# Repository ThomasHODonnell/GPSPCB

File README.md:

# GPS PCB - designing a consumer electronic from start to finish

## *Concepts*
- My father run a bicycle shop. Some of his customers' bicycles have been stolen. He asked me if I could design a product to help combat this problem. This problem led me to a GPS based solution - to get things started. 
- The solution provided here is an embedded system that can transmit its location upon request utilizing a satallite HTTP request API.
- This product combats the problem by not only locating a stolen / lost bicycle, but my locating a potential thief. Therefore, this product can act as a form of location verification for law enforcement bodies in pursuit of any item this PCB is attached to. 

## *Logistics* 
- I have designed 3D printed CAD models to safely secure this system on a moving bicycle. This system comfortably holds the PCB, its components and a battery. 
- While I have not completed suffient testing to determine the battery life of this system, its power consumption is very low for a reasonably sized battery and its capacity. This combination should ensure that the device does not need to be recharged for a reasonable amount of time. 

## Technical Information
- This initial design is intended to be minimalistic. I have foregone a Microcontroller Unit in an effort to minimize power consumption, size, and cost. Alternativly, I have implemented a standalone Reciever / Transciever combination to complete the necessary funcitonality without any additional computing. 
- Of course, there are a number of other ICs to accompany these functional components, such as LDO Regulators, Operational Amplifiers, Logic Gates, Switches, Battery IC, Low Noise Amplifier, and Antennas.  
- While this Electronic Circuit requires significantly more testing, the technical aspectrs of this solution offer a helpful initial solution to a logicically challenging problem. 

## Disclaimer
- I am a third-year Computer Engineering Student. In no fashion am I qualified to develop professional grade products at this point in my career. 
- Therefore, I would not recommend using any of my design choices for other applications without inquiring a professional. 
- I will post other README files within other folders with other information, screenshots, and files.

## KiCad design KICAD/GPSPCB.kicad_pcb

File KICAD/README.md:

# Kicad Files

## *This folder contains files needed to open / edit this project in KICAD.* 

- I'll use these files to provide screenshots from the IMAGES folder for your entertainment!
- This file could also be considered as a BOM, but i'll leave out component prices as they fluctuate frequently. 
- The PCB should be finished with production within the next week or so (7/27/23), after which I will upload real images of the device.

### **Electrical Schematics** 

#### Complete Schematic

#### LDO and Battery IC
- LDO(1.8V): LT1963A - Linear Technology
-  Rechargable Battert IC: BQ24092 - T.I.

#### Reciever
- RF Reciever: STA8090FG - STM32MicroElectronics
- 

#### Transciever
- RF signal transciever: SX1268IMLTRT - Semtech Corp. 

#### Various Components
- Op-Amp: TL081HIDBVR - T.I.
- LNA: SKY65404-31 - Skyworks
- Input Antenna: 1575AT43A0040001E - Johanson
- SPDT RF Switch: PE4259 - Pasternack
- Output Antenna: A10340 - Antenova
- Dual NAND Gate: 74LVC2G00GT,115 - Nexperia
- Water Resistant USBC Port: DX07S016JA1R1500 - JAE Elec. 
- 32 MHZ Crystal: FC-12M 32.7680KD-A0 - EPSON

### **PCB Schematics**
- I will only show a screenshot of the Front Copper layer, as all of the components are located on this layer. 
- If interested, I welcome a detailed review of the PCB design through the direct file found in this folder. 
- DISCLAIMER: I AM NOT EMPLOYED BY PROTECTION AUTOMATED. I am interested in entrepreneurship in the future. 
If testing proves that a version of this product could become viable, I wanted to label the project as that businesses prototype. 

- A 3D view for a more clear image.

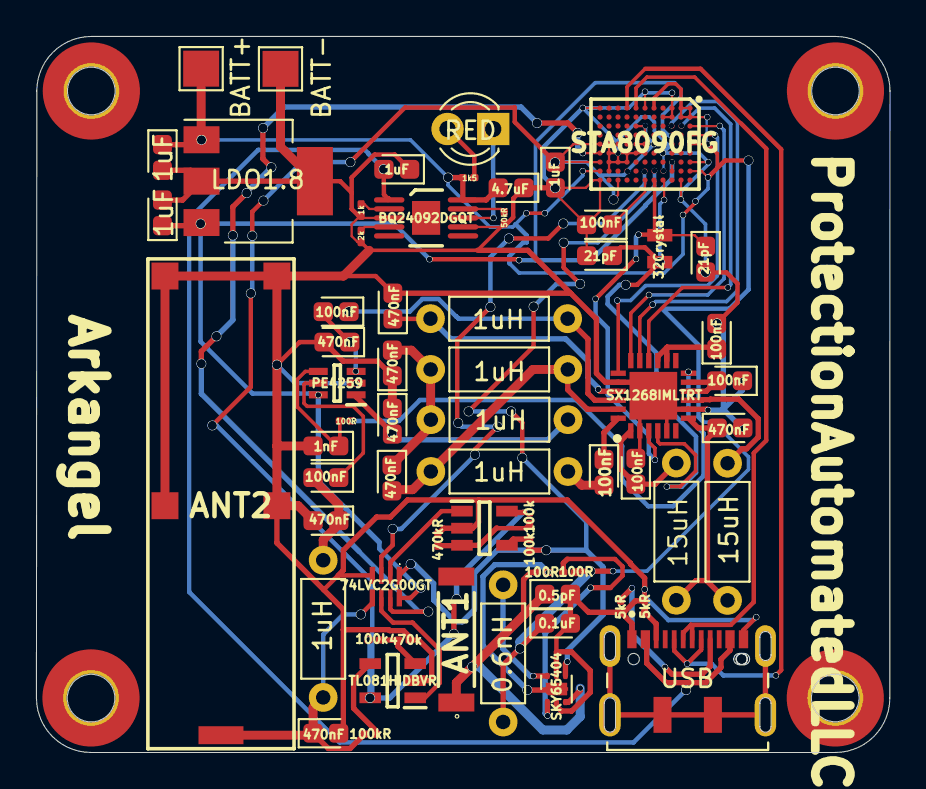
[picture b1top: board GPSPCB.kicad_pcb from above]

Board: 2 copper layers, 47.4 x 39.8 mm, 68 parts (0 on the bottom side), 52 nets.

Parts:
ANT1: 1575AT43A0040E
ANT2: A10340
C4, C5: 21pF; CP_EIA-1608-08_AVX-J
C6, C7, C11, C15: 1uF; CP_EIA-1608-08_AVX-J
C8: 0.1uF; CP_EIA-1608-08_AVX-J
C9: 0.5pF; CP_EIA-1608-08_AVX-J
C10: 4.7uF; CP_EIA-1608-08_AVX-J
C12, C16, C17, C18, C22, C24: 100nF; CP_EIA-1608-08_AVX-J
C13, C14, C19, C20, C21, C23, C25, C26: 470nF; CP_EIA-1608-08_AVX-J
C27: 1nF; CP_EIA-1608-08_AVX-J
Ce: 100nF; CP_EIA-1608-08_AVX-J
D2: RED; LED_D3.0mm
H1, H2, H3, H4: MountingHole; MountingHole_2.7mm_M2.5_Pad_TopOnly
IC1: STA8090FG; BGA99C50P9X11_500X600X120
IC2, IC5: TL081HIDBVR; SOT95P280X145-5N
IC3: SX1268IMLTRT; QFN50P400X400X100-25N-D
IC4: PE4259; SOT65P210X110-6N
IC6: 74LVC2G00GT; 74AVC9112GTX
J1: USB; JAE_DX07S016JA1R1500
L1: 0.6nH; L_Axial_L5.3mm_D2.2mm_P7.62mm_Horizontal_Vishay_IM-1
L2, L5, L7, L8: 1uH; L_Axial_L5.3mm_D2.2mm_P7.62mm_Horizontal_Vishay_IM-1
L3, L4: 15uH; L_Axial_L5.3mm_D2.2mm_P7.62mm_Horizontal_Vishay_IM-1
Le: 1uH; L_Axial_L5.3mm_D2.2mm_P7.62mm_Horizontal_Vishay_IM-1
R1, R3, R12: 100R; R_0201_0603Metric
R2, R8: 5kR; R_0201_0603Metric
R4: 1k; R_0201_0603Metric
R5: 2k; R_0201_0603Metric
R6: 50kR; R_0201_0603Metric
R7: 1k5; R_0201_0603Metric
R9, R11, R15: 100k; R_0201_0603Metric
R10: 470kR; R_0201_0603Metric
R14: 100kR; R_0201_0603Metric
R16: 470k; R_0201_0603Metric
TP1: BATT+; TestPoint_Pad_2.0x2.0mm
TP2: BATT-; TestPoint_Pad_2.0x2.0mm
U2: SKY65404; Skyworks_SKY65404-31
U3: LDO1.8; SOT-223-3_TabPin2
U4: BQ24092DGQT; DGQ0010D_NV_N
Y2: 32Crystal; FC12M327680KDA0

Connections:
+1V0: C6.1, C8.1, C10.2, IC1.A1 (VINM_1), IC1.A2 (VINM_2), IC1.A5 (VINL1), IC1.A8 (VINB), IC1.B1 (VLX_1), IC1.B2 (VLX_2), IC1.E1 (VDD_ANA), IC1.L8 (VINL2), L1.2, R3.2, R7.1, TP1.1, U3.1 (IN), U4.10 (OUT)
+1V1: C15.1, IC1.E5 (VDDD_1), IC1.F3 (VDDD_2), IC1.F4 (VDDD_3), IC1.G3 (VDDD_4), IC1.H8 (VCC_PLL), IC1.J9 (VCC_CHAIN), IC1.L5 (VCC_RF), IC1.L7 (VOL2), IC2.5 (V+), IC5.5 (V+), R9.1, R15.1
+1V5: C7.1, IC1.C4 (VDDIO__R1), IC1.C7 (VDD_SQI), IC1.C8 (VDD__ADC), IC4.6 (~CTRL_OR_VDD), IC6.8 (VCC), U3.3 (OUT)
-BATT: ANT2.1, ANT2.2, ANT2.3, ANT2.4, C4.2, C5.2, C6.2, C7.2, C8.2, C9.2, C10.1, C11.1, C12.2, C14.2, C15.2, C17.1, C18.2, C19.1, C20.1, C21.2, C23.2, C25.2, C26.2, C27.2, Ce.2, IC1.A7 (GND_1), IC1.B9 (GND_2), IC1.C1 (GND_3), IC1.C2 (GND_4), IC1.D2 (GND_5), IC1.D6 (GND_6), IC1.D8 (GND_7), IC1.F1 (GND_8), IC1.F5 (GND_9), IC1.F6 (GND_10), IC1.G4 (GND_11), IC1.G5 (GND_12), IC1.G6 (GND_13), IC1.H6 (GND_14), IC1.H7 (GND_15), IC1.J6 (GND_16), IC1.J7 (GND_17), IC1.K5 (GND_18), IC1.K6 (GND_19), IC1.K7 (GND_20), IC1.K8 (GND_LNA), IC1.L1 (GND_21), IC1.L9 (GND_22), IC2.2 (V-), IC3.2 (GND_1), IC3.5 (GND_2), IC3.8 (GND_3), IC3.20 (GND_4), IC3.25 (GND_5), IC4.2 (GND), IC5.2 (V-), IC6.4 (GND), J1.1 (GND), J1.12 (GND), R2.1, R4.2, R5.2, R6.2, R8.1, R10.2, R16.2, TP2.1, U2.2 (GND), U2.5 (GND), U3.2 (GND), U4.3 (VSS), U4.7 (ISET2)
ANTOUT: ANT2.5 (FEED), C26.1, IC6.5 (2A), L8.1, R14.1
BATTICIN: C11.2, J1.2 (VBUS), J1.11 (VBUS), U4.1 (IN)
CrystalA: C5.1, IC1.E9 (RTC_XTI), IC3.3 (XTA), Y2.1
CrystalB: C4.1, IC1.D9 (RTC_XTO), IC3.4 (XTB), Y2.2
D+: IC1.G1 (USB_DP), J1.6 (D+), J1.7 (D+)
D-: IC1.H1 (USB_DM), J1.5 (D-), J1.8 (D-)
DIO2: IC3.12 (DIO2), R12.2
LNA_IN: IC1.L6 (LNA_IN), IC6.7 (1Y)
LNA_OUT: IC1.E8 (WAKEUP0), IC6.1 (1A), R11.1, U2.4 (RFOUT)
MISO: IC1.B3 (SPI_DI), IC3.16 (MISO)
MOSI: IC1.C3 (SPI_DO), IC3.17 (MOSI)
NSS: IC1.A4 (SPI_CSN), IC3.19 (NSS)
unnamed: ANT1.1 (FEED), C9.1, R1.2, U2.3 (RFIN)
unnamed: C13.1, C19.2, L5.1, Le.2
unnamed: C16.2, L2.2
unnamed: C24.2, C25.1, L8.2
unnamed: D2.2 (A), R7.2
unnamed: D2.1 (K), U4.8 (CHG_N)
unnamed: Ce.1, IC1.F9 (RSTN)
unnamed: IC2.3 (IN+), R9.2, R10.1
unnamed: IC2.4 (IN-), R11.2
unnamed: C12.1, IC3.14 (BUSY), IC3.15 (NRESET)
unnamed: IC3.9 (DCC_SW), L4.2
unnamed: C22.1, IC3.22 (RFI_N), L7.2
unnamed: C21.1, IC3.21 (RFI_P), L7.1
unnamed: C13.2, IC3.23 (RFO), L2.1, L5.2
unnamed: C17.2, IC3.10 (VBAT), IC3.11 (VBAT_IO)
unnamed: C18.1, IC3.1 (VDD_IN), L3.2
unnamed: C14.1, IC3.7 (VREG), L3.1, L4.1
unnamed: C16.1, IC3.24 (VR_PA)
unnamed: C27.1, IC4.4 (CTRL), R12.1
unnamed: C24.1, IC4.5 (RFC)
unnamed: IC5.3 (IN+), R15.2, R16.1
unnamed: IC5.4 (IN-), R14.2
unnamed: J1.3 (CC1), R8.2
unnamed: J1.9 (CC2), R2.2
unnamed: R1.1, U2.7 (EP)
unnamed: L1.1, U2.6 (VCC)
unnamed: R3.1, U2.1 (VENABLE)
unnamed: R4.1, U4.2 (ISET)
unnamed: R5.1, U4.4 (PRE-TERM)
unnamed: R6.1, U4.9 (TS)
OP1_OUT: IC2.1 (OUT), IC6.2 (1B)
OutDelayed: IC5.1 (OUT), IC6.6 (2B)
RF1: C20.2, IC4.1 (RF1), Le.1
RF2: C22.2, C23.1, IC4.3 (RF2)
SLEEP: IC1.F8 (STDBYN), IC6.3 (2Y)
SPICLK: IC1.A3 (SPI_CLK), IC3.18 (SCK)

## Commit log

2023-07-28 Update!
2023-07-28 uploading 3D view
2023-08-05 adding JSON files
